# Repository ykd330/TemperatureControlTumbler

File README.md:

Code Editor 형식으로 변환해서 보시는 걸 추천합니다.

한경대학교 2025 졸업작품 softWare
주제 : 온도 조절 텀블러
제작기간 : 2025.03.04 ~ 2025.05.28
제작 팀 : 온도 조절 텀블러 조 (5조)
softWare설계 및 제작 담당 : 유경도
담당교수 : 김수찬교수님

Development Environment :
Dev tool : VSCode (Platform IO) + Arduino IDE(Test 및 Serial통신) <- VSCode에서 CDC boot 옵션 설정이 제공되지 않아 임의의 Serial통신이 불가능
Simulation : Wokwi Simulator(ESP32-C3)

used Library : 
1. arduino.h 
2. u8g2.h (Display)
3. Wire.h (I2C)
4. OneWire (Sensors Transmission)
5. DallasTemperature (Sensors Control)
6. FS.h / LittleFS.h (File Save )
7. SparkFun_MAX1704x_Fuel_Gauge_Arduino_Library.h (FuelGauge)

GPIO_PIN
COOLER_PWM_PIN = 1, // PWM
HEATER_PWM_PIN = 2, // PWM
ONE_WIRE_BUS = 3,   // DS18B20 센서 핀
BUTTON_BOOT = 5,    // 모드 변경 버튼
BUTTON_UP = 6,      // 설정온도 상승 버튼
BUTTON_DOWN = 7,    // 설정온도 하강 버튼
SDA_I2C = 8,        // Hardware에서 설정된 I2C핀
SCL_I2C = 9,        // Hardware에서 설정된 I2C핀
COOLING_PAN = 10,
COOLER_PIN = 20,    // 냉각 제어 핀
HEATER_PIN = 21     // 가열 제어 핀

구현 기능 : 
코드 흐름도 : [코드 흐름도.pdf](https://github.com/user-attachments/files/20577649/default.pdf)

Device Mode :
0. Boot Mode :
최초 전력 공급 시 자동으로 진입되는 모드
약 3초 후 자동으로 Stanby Mode로 진입

1. Stanby Mode :
Feltier : 온도 제어 X
Display : 현재 온도, 배터리 상태만 출력
*Boot 버튼을 통해 Temperature

2. Active Mode : 
Feltier : 현재온도와 설정온도를 비교하여 가열 / 냉각 수행
Display : 현재온도, 목표온도, 배터리 잔량(%), 온도변화 애니메이션, 가열 / 냉각 출력
*온도 조절이 종료되면 자동으로 T.M Mode로 진입
*Up / Down 버튼을 통해 작동 중에도 설정온도 변경이 가능
*Boot 버튼을 통해 종료 가능

3. Temperature Maintanence Mode :
Feltier : 현재온도와 설정온도의 차이가 심해지면 작동하여 온도 유지
Display : 현재온도, 배터리 상태 출력

4. Temperature Setting Mode :
Display : 목표 온도 표기 / 전용 Display 출력 화면
Button : Up / Down 버튼으로 설정온도를 조절, Boot Button으로 온도를 확정
*함수 종료시 설정된 온도를 기준으로 Active 모드와 T.M 모드를 자동으로 선택하여 작동
*Boot 버튼을 통해 종료 가능

5. Sleep Display :
약 5분동안 버튼의 입력이 없으면 자동으로 Display는 절전모드로 진입
버튼 입력 시 절전모드 해제 / 절전모드 상태에서 버튼 입력은 절전모드 해제에만 사용됨

6. reboot :
boot버튼을 5초 이상 누르면 강제로 재부팅함

H-Bridge Control :
1. Logic 핀 2개와 PWM핀 2개로 제어
2. 드라이버 특성상 두개의 logic 핀은 작동시 high로 설정
3. PWM핀을 통해 전류의 흐름 및 전류량을 제어함
4. 단 두 PWM핀에 동시에 PWM이 인가될 경우 드라이버 과열로 손상 가능성 있으므로 소프트웨어적으로 delay를 추가함

프로젝트 진행 결과 및 개인적 고찰 :
2025.06.04 :
결과 : 냉각기능 구현 실패 / 가열기능 약 62℃까지 가능 (단열 시 증가 여지 있음)
고찰 :
1. 펠티어소자의 발열량이 생각보다 매우 크므로 이를 제어할 수 있는 냉각 솔루션을 구현해야한다.
2. 펠티어소자의 발열량과는 별개로 텀블러에서 받아들이는 열량이 생각보다 적다. 이를 해결하지 못하면 빠르게 물의 온도를 올리는 것은 불가능할 것으로 보인다.
-> 텀블러의 소재 변경이나 switching 방식으로 여러 펠티어소자를 부착하여 시간마다 발열점을 바꾸어 주는 방식, 고 열전도 물질을 사용하여 텀블러 외부를 감싸고 내부에 써멀 패드나 써멀 그리스를 사용하여 열전도율을 최대한 끌어내는 방식 고려중
3. 텀블러 내부에 사용할 수 있는 공간이 매우 적다. 최대한 효율적인 배치로 쿨링 팬의 공기의 흐름을 방해하지 않으면서 배선하기 쉽지 않으므로 외부 설계 시 이러한 점을 최대한 고려해야 함을 알았다.

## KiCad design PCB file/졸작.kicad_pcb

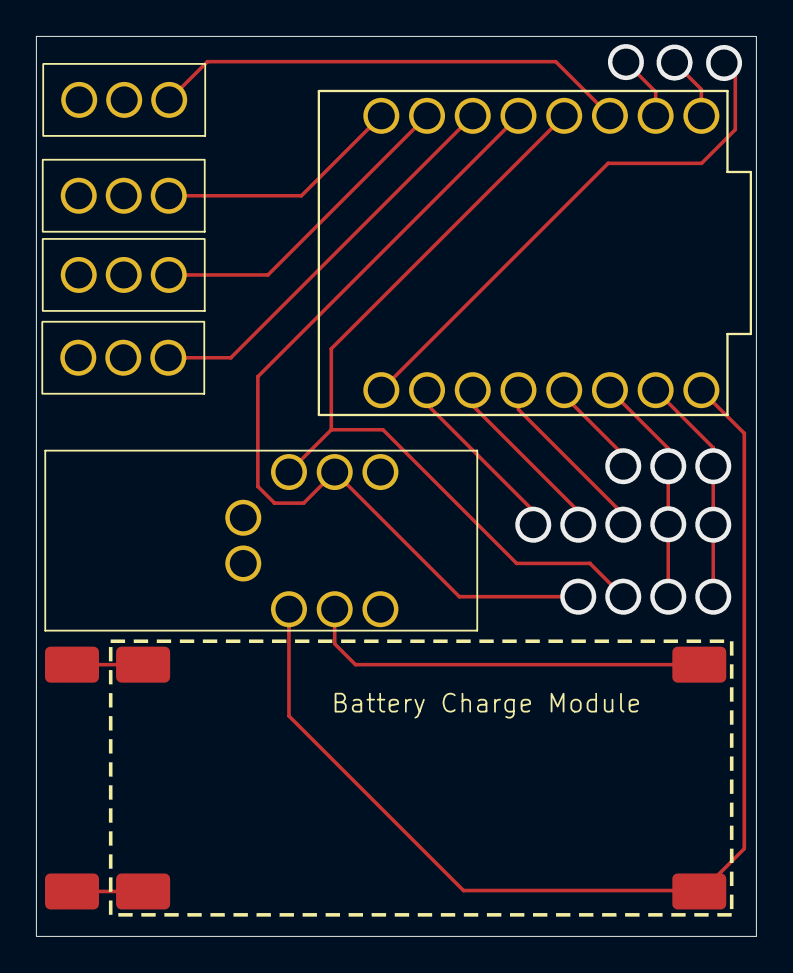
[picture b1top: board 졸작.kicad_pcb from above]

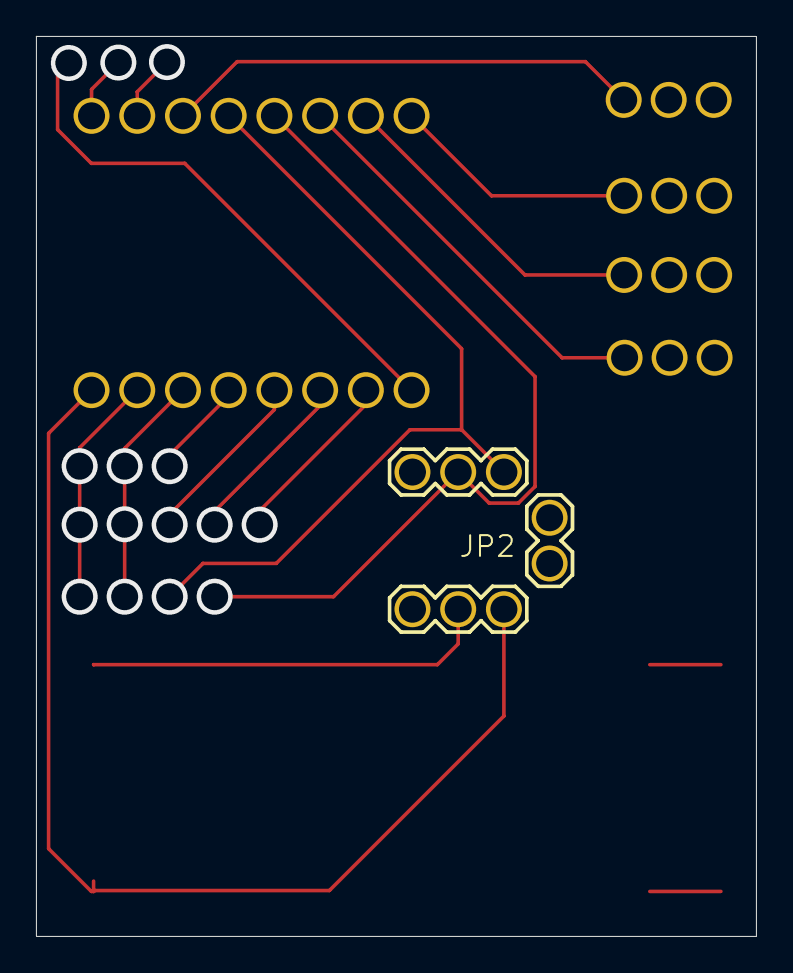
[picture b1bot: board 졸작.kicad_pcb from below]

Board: 2 copper layers, 40.0 x 50.0 mm, 5 parts (3 on the bottom side), 4 nets.

Parts:
ESP32-C3
SuperMini: MODULE_ESP32-C3_SUPERMINI
JP2, JP4: 1X03
JP5: 1X02
PAD: F_MASK SMD PAD

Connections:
GND: ESP32-C3 SuperMini.G, JP4.2, JP5.2
SCL: ESP32-C3 SuperMini.9, JP2.2
SDA: ESP32-C3 SuperMini.8, JP2.1
VCC: ESP32-C3 SuperMini.3.3, ESP32-C3 SuperMini.5V, JP4.1, JP5.1, PAD.A

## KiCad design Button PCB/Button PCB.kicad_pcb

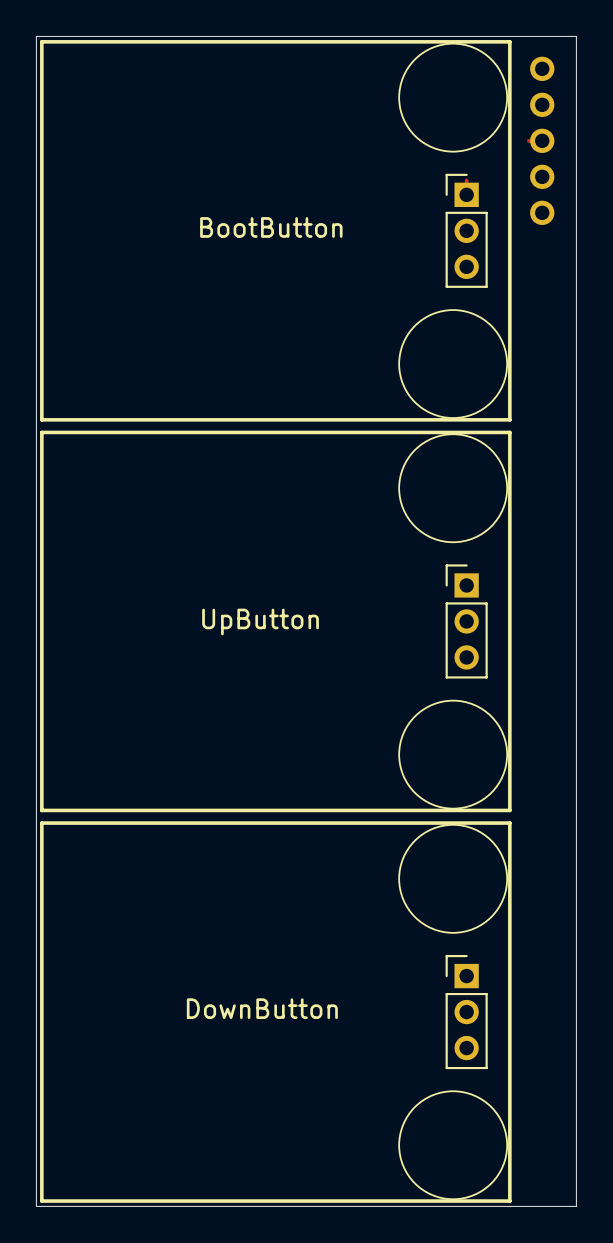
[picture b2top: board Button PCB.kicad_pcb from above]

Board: 2 copper layers, 30.0 x 65.0 mm, 3 parts (0 on the bottom side), 2 nets.

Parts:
BootButton: PinHeader_1x03_P2.00mm_Vertical
DownButton: PinHeader_1x03_P2.00mm_Vertical
UpButton: PinHeader_1x03_P2.00mm_Vertical

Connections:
GND: BootButton.3, DownButton.3, UpButton.3
VCC: BootButton.2, DownButton.2, UpButton.2

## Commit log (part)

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2025-04-09 Add main.cpp
2025-04-09 ad main
2025-04-12 fix display print
2025-04-12 Main System and Display fix
2025-04-13 Button Interrupt logic fix
2025-04-13 add Main Display System and Battery Print Function
2025-04-14 Update main.cpp
    test
2025-04-14 Use class
2025-04-14 add header
2025-04-15 fix bug...
2025-04-15 fix system logic
2025-04-16 Update main.cpp
    fix button logic
2025-04-16 Update main.cpp
    change font
2025-04-17 Update main.cpp
    bug hhhhh
2025-04-18 fix systemlogic
2025-04-30 shyncro
2025-04-30 fixed button logic
2025-05-05 display print fix
2025-05-07 TM fix
2025-05-07 dlrj dho dksehowl
2025-05-09 fix button logic in Temperature maintanence mode
2025-05-09 fix bug in display and button -> bootbutton logic
2025-05-11 use PULL_DOWN in interrupt
2025-05-11 fix bug -> button / display print
2025-05-11 dho dksehowl wlsWKfh
2025-05-12 bug fix -> can't access ActiveMode
2025-05-12 add detect pushed button logic in Display_Sleep device mode
2025-05-13 fix bug and codes logic
2025-05-13 fix codes Logic
2025-05-13 add function and fix bug
2025-05-13 add BatteryCheck logic, Active -> TM mode change display, PWM and PWM set fix PWM logic, TM mode logic and change condition for Active -> TM mode
2025-05-14 fix define limit temperature codes
2025-05-14 fix TM mode bug
2025-05-14 add Up&Down Button Toggle Logic -> bug
2025-05-15 add Up and Down button Toggle logic -> control Temperature
2025-05-16 add function - returnTextWidthPixel
2025-05-16 fix reboot logic
2025-05-18 fix code and add PWM_PIN for control feltier unit
2025-05-18 Test Battery System and fix Battery logic
2025-05-19 add Library for BatteryInfo
    get Battery Info
2025-05-20 change Battery logic
2025-05-21 fix I2C Transmission - Two Bus -> One Bus
2025-05-23 Main PCB Data
2025-05-23 change branch
2025-05-23 Add Button PCB
2025-05-23 add PDF
2025-05-24 add Error detect logic for DRV8833 Moter Drive Module and fix Feltier control logic
2025-05-27 update new logic
2025-05-28 change bit logic
2025-05-28 fix bug
2025-05-28 change Pin
2025-05-30 fix bug and PWM logic
2025-05-31 Change PCB file
2025-05-31 add COOLING_PAN
2025-05-31 bug fix : setUp PWM ledcSetup pin -> channel
2025-06-01 state logic
2025-06-07 Update size 40 x 50
2025-06-07 fix size PCB 50X40 / add MOSFET hole
2025-06-16 fixed for PCB
